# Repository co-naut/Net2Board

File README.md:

# Net2Board

A Python engine that turns design intent into legal geometry. An external AI orchestrator states the relations — "these decoupling caps within 2 mm of U1's power pins", "the power section in this region of the board" — and Net2Board solves for the exact integer coordinates: budgeted deterministic placement search, exact integer-nanometre geometric checks, and byte-deterministic `.kicad_pcb` and Specctra DSN export that KiCad and Freerouting open natively.

## Ambition

1. **Intent to geometry** — relational constraints in (Requirements and Preferences on a Board), exactly-solved legal placements out
2. **The engine layer beneath AI orchestrators** — the orchestrator states intent and judges outcomes in tens of calls; the engine's inner loop evaluates candidates algorithmically, with no oracle call in the path — a wrapper shelling out to a slow oracle for every candidate cannot follow at any price
3. **Exactness as the contract** — integer nanometres, deterministic results given the arguments, `kicad-cli` as the cross-checking DRC authority (Net2Board is not the sign-off oracle)
4. **Routing delegated, not searched** — a pure DSN handoff to Freerouting; routed copper re-enters the loop as intent, never as engine state

Out of scope: orchestrator skills and PCB-design conventions, simulation (SI/PI/thermal/EM), a second EDA input format, MCP/orchestrator transport, being a KiCad wrapper or an end-user product.

## Development

Requires [uv](https://docs.astral.sh/uv/).

```console
uv sync                     # set up the environment (Python 3.12)
uv run ruff check           # lint
uv run ruff format --check  # format check
uv run pytest               # fast-tier tests
```

## Measured

Both ratios come from one run on one machine — self-normalizing, and asserted ≥1,000× by the slow-tier tests (`uv run pytest -m slow`; requires kicad-cli). The routing beats are a separate opt-in tier (`uv run pytest -m route`; needs java, the sha-pinned Freerouting jar, system pcbnew, and kicad-cli — the human baseline re-measures only under `NET2BOARD_REMEASURE_HUMAN=1`).

| scope | engine | wrapper (kicad-cli per candidate) | ratio |
|---|---|---|---|
| per-candidate (ecc83, micro) | 98.9 µs/candidate | 2.578 s | 26,075× |
| per-session (tiny_tapeout, macro) | 200.61 s for 1,249,767 candidates (typical move 71.6 µs/probe) | 3,366,460.8 s derived — 2.693671 s × 1,249,767 | 16,781× |

## Routed

The M3 benchmark (ADR-0024): both placements routed under identical rules — `DesignRules()` 0.2/0.5 mm + `RouteSizes()` 0.25/0.8 mm, the same sha-pinned freerouting-2.4.1 jar and arguments. Enforced: the unrouted comparison (solver ≤ human) and zero enforced copper findings before routing, under both judges; after routing, each enforced type reads no worse than the human board's row (here: cleaner on all four). Reported, never enforced: the COMPLETED states, the violation tallies, the walls. Reproduce with `uv run pytest -m "slow or route"` (~50 min with the human gate off).

| fixture | placement | state | unrouted | router violations | enforced post-route (shorts/crossings/clearance/edge) | router wall |
|---|---|---|---|---|---|---|
| tiny_tapeout | human (demo placement, pinned) | COMPLETED | 71 | 45 | 3 / 0 / 1 / 2 | pinned |
| tiny_tapeout | solver (knob off) | COMPLETED | 61 | 18 | 0 / 0 / 0 / 0 | ≈32 min (derived) |

Fixtures: ecc83 (15 comps / 9 nets) and tiny_tapeout (150 comps / 114 nets, 104.5 × 81 mm, 4 Cu). Oracle: kicad-cli 10.0.7; freerouting-2.4.1 (sha256-pinned). Linux x86_64, Python 3.12.12. The macro row's derived baseline prices the counterfactual wrapper engine: real `kicad-cli pcb drc` runs on fully placed boards of the same fixture, times the session's candidate count.

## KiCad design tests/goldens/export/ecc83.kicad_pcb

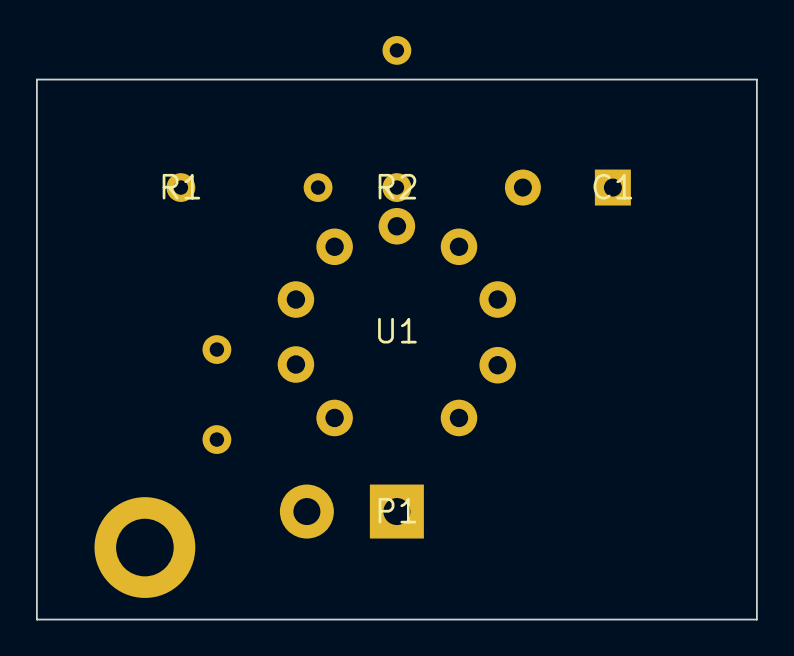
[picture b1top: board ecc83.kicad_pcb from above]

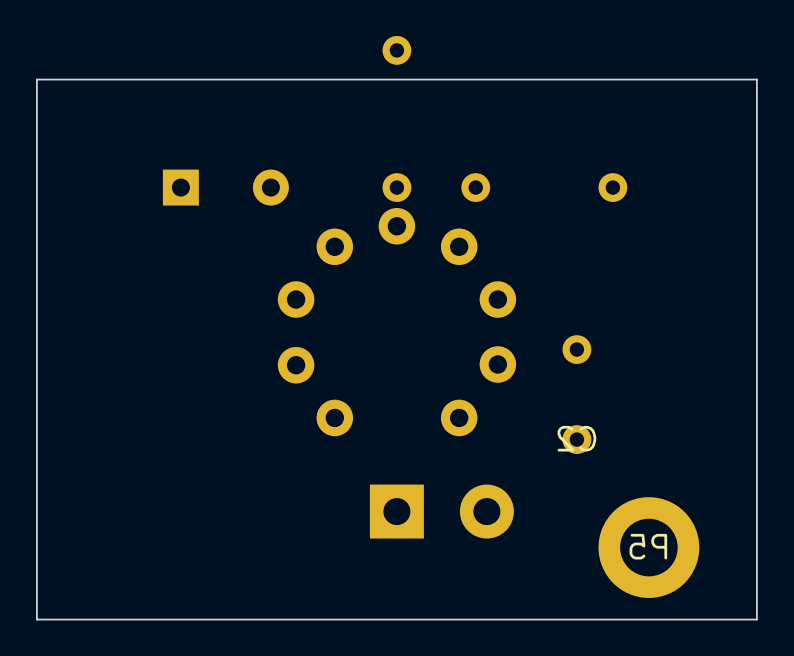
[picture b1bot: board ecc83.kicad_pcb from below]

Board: 2 copper layers, 40.0 x 30.0 mm, 7 parts (2 on the bottom side), 7 nets, no tracks yet.

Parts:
C1: CP_Radial_D10.0mm_P5.00mm
C2: C_Disc_D4.7mm_W2.5mm_P5.00mm
P1: Altech_AK300_1x02_P5.00mm_45-Degree
P5: MountingHole_3.2mm_M3_DIN965_Pad
R1, R2: R_Axial_DIN0207_L6.3mm_D2.5mm_P7.62mm_Horizontal
U1: Valve_ECC-83-1

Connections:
GND: C1.2, P1.1, R2.2
unnamed: P1.2, U1.2
unnamed: C1.1, U1.6
unnamed: U1.4, U1.5
unnamed: R1.1, U1.1, U1.7
unnamed: C2.2, R1.2, U1.8
unnamed: R2.1, U1.3
